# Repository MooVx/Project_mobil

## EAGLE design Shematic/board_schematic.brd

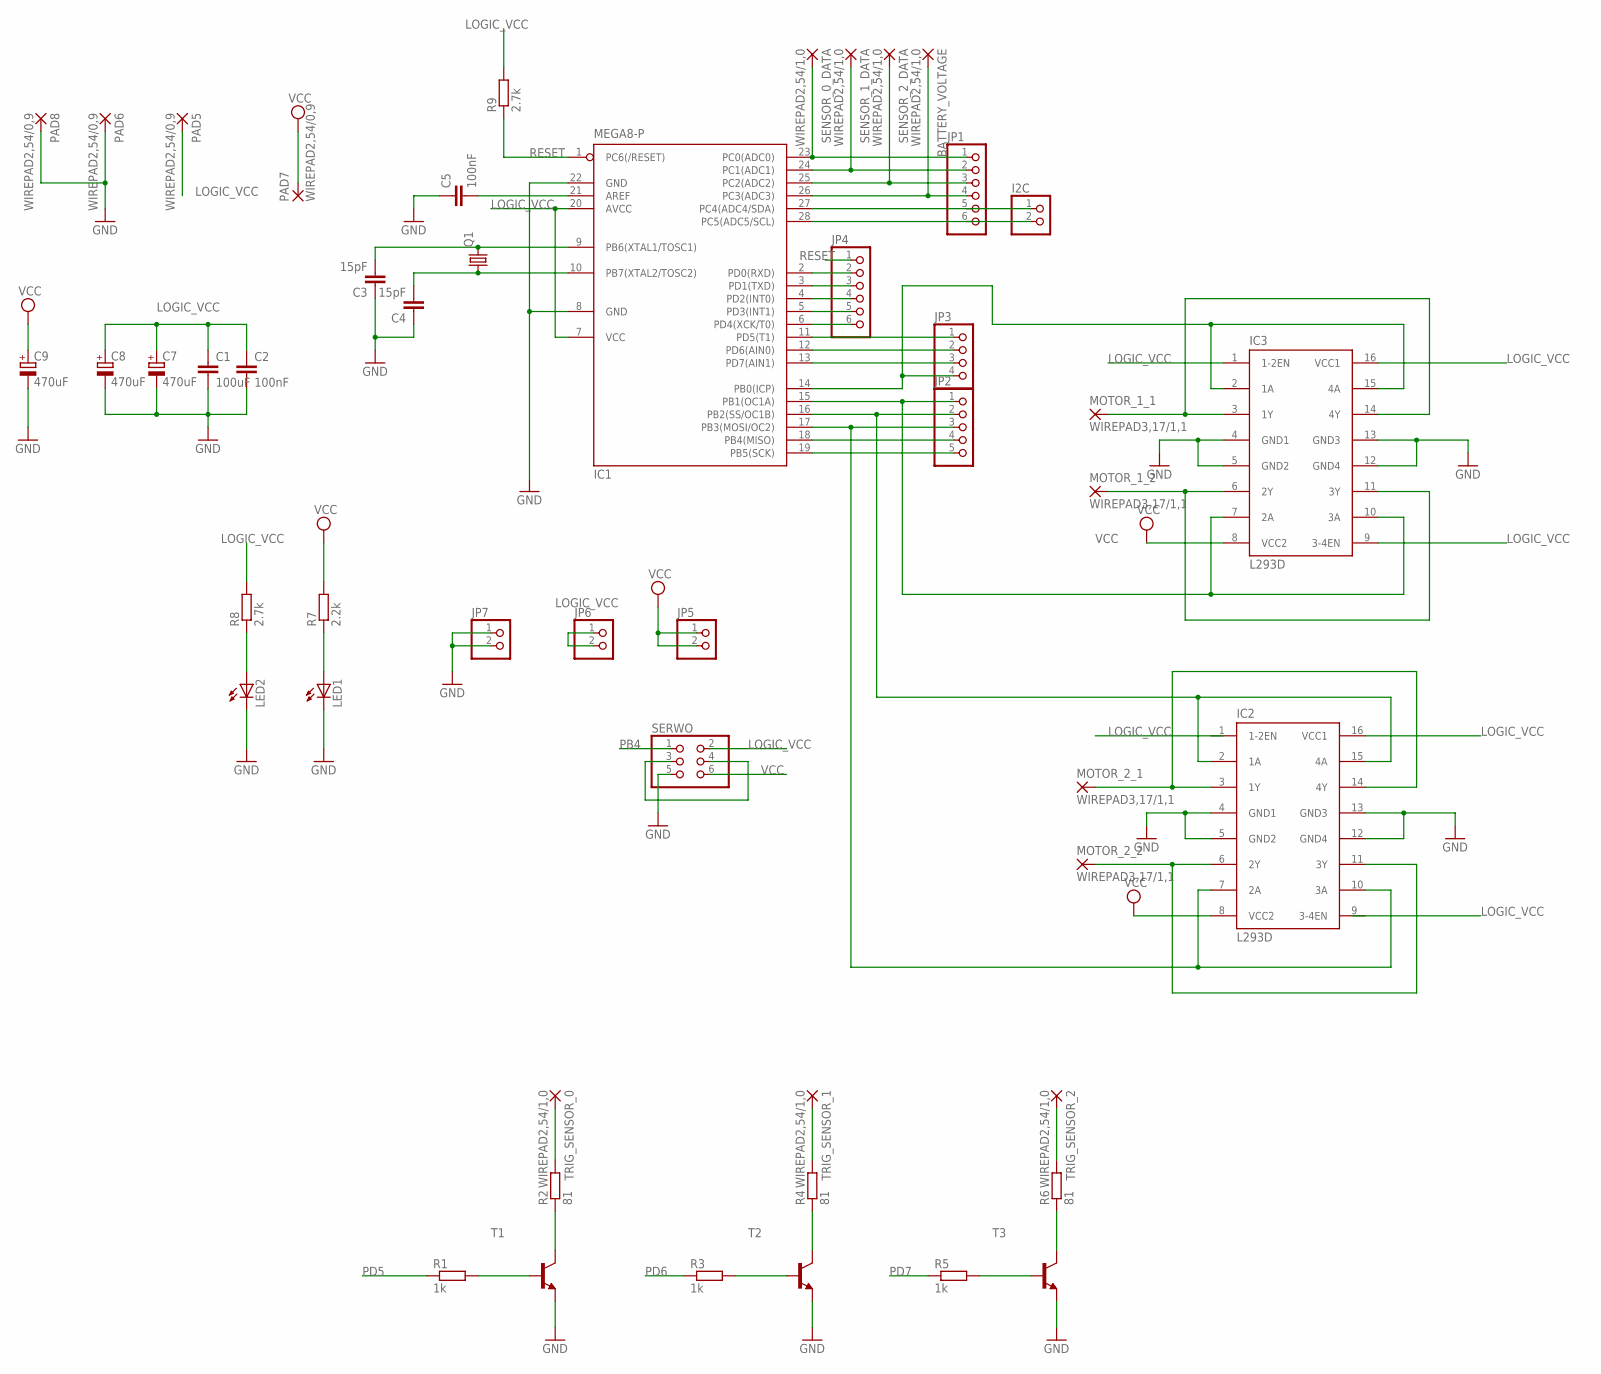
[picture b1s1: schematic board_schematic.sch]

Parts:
BATTERY_VOLTAGE: WIREPAD2,54/1,0; 2,54/1,0
C1: 100uF; C050-045X075
C2, C5: 100nF; C050-045X075
C3, C4: 15pF; C5B2.5
C7, C8, C9: 470uF; E3,5-8
I2C: PINHD-1X2; 1X02
IC1: MEGA8-P; DIL28-3
IC2, IC3: L293D; DIL16
JP1, JP4: PINHD-1X6; 1X06
JP2: PINHD-1X5; 1X05
JP3: PINHD-1X4; 1X04
JP5, JP6, JP7: PINHD-1X2; 1X02
LED1, LED2: LED5MM
MOTOR_1_1, MOTOR_1_2, MOTOR_2_1, MOTOR_2_2: WIREPAD3,17/1,1; 3,17/1,1
PAD5, PAD6, PAD7, PAD8: WIREPAD2,54/0,9; 2,54/0,9
Q1: CRYSTALHC49S; HC49/S
R1, R3, R5: 1k; 0204/7
R2, R4, R6: 81; 0204/7
R7: 2.2k; 0204/7
R8, R9: 2.7k; 0204/7
SENSOR_0_DATA, SENSOR_1_DATA, SENSOR_2_DATA: WIREPAD2,54/1,0; 2,54/1,0
SERWO: PINHD-2X3; 2X03
T1, T2, T3: 2N2222-NPN-TO92-EBC; TO92-EBC
TRIG_SENSOR_0, TRIG_SENSOR_1, TRIG_SENSOR_2: WIREPAD2,54/1,0; 2,54/1,0

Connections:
BLABLA: I2C.1, IC1.27 (PC4(ADC4/SDA)), JP1.5
GND: C1.2, C2.2, C3.1, C4.1, C5.1, C7.-, C8.-, C9.-, I2C.3, IC1.8 (GND), IC1.22 (GND), IC2.4 (GND1), IC2.5 (GND2), IC2.12 (GND4), IC2.13 (GND3), IC3.4 (GND1), IC3.5 (GND2), IC3.12 (GND4), IC3.13 (GND3), JP7.1, JP7.2, LED1.K (C), LED2.K (C), PAD6.1, PAD8.1, SERWO.5, T1.E, T2.E, T3.E
LOGIC_VCC: C1.1, C2.1, C7.+, C8.+, IC1.7 (VCC), IC1.20 (AVCC), IC2.1 (1-2EN), IC2.9 (3-4EN), IC2.16 (VCC1), IC3.1 (1-2EN), IC3.9 (3-4EN), IC3.16 (VCC1), JP6.1, JP6.2, PAD5.1, R8.2, R9.2, SERWO.2
unnamed: IC3.3 (1Y), IC3.14 (4Y), MOTOR_1_1.1
unnamed: IC1.15 (PB1(OC1A)), IC3.7 (2A), IC3.10 (3A), JP2.1
unnamed: IC2.3 (1Y), IC2.14 (4Y), MOTOR_2_1.1
unnamed: IC1.16 (PB2(SS/OC1B)), IC2.2 (1A), IC2.15 (4A), JP2.2
unnamed: R1.2, T1.B
unnamed: IC2.6 (2Y), IC2.11 (3Y), MOTOR_2_2.1
unnamed: IC3.6 (2Y), IC3.11 (3Y), MOTOR_1_2.1
unnamed: IC1.17 (PB3(MOSI/OC2)), IC2.7 (2A), IC2.10 (3A), JP2.3
unnamed: IC1.23 (PC0(ADC0)), JP1.1, SENSOR_0_DATA.1
unnamed: C3.2, IC1.9 (PB6(XTAL1/TOSC1)), Q1.2
unnamed: C4.2, IC1.10 (PB7(XTAL2/TOSC2)), Q1.1
unnamed: C5.2, IC1.21 (AREF)
unnamed: IC1.24 (PC1(ADC1)), JP1.2, SENSOR_1_DATA.1
unnamed: IC1.25 (PC2(ADC2)), JP1.3, SENSOR_2_DATA.1
unnamed: BATTERY_VOLTAGE.1, IC1.26 (PC3(ADC3)), JP1.4
unnamed: I2C.2, IC1.28 (PC5(ADC5/SCL)), JP1.6
unnamed: LED1.A, R7.1
unnamed: IC1.19 (PB5(SCK)), JP2.5
unnamed: IC1.6 (PD4(XCK/T0)), JP4.6
unnamed: IC1.5 (PD3(INT1)), JP4.5
unnamed: IC1.4 (PD2(INT0)), JP4.4
unnamed: IC1.3 (PD1(TXD)), JP4.3
unnamed: IC1.2 (PD0(RXD)), JP4.2
unnamed: SERWO.3, SERWO.4
unnamed: LED2.A, R8.1
unnamed: IC1.14 (PB0(ICP)), IC3.2 (1A), IC3.15 (4A), JP3.4
unnamed: R2.1, T1.C
unnamed: R2.2, TRIG_SENSOR_0.1
unnamed: R3.2, T2.B
unnamed: R4.1, T2.C
unnamed: R4.2, TRIG_SENSOR_1.1
unnamed: R5.2, T3.B
unnamed: R6.1, T3.C
unnamed: R6.2, TRIG_SENSOR_2.1
PB4: IC1.18 (PB4(MISO)), JP2.4, SERWO.1
PD5: IC1.11 (PD5(T1)), JP3.1, R1.1
PD6: IC1.12 (PD6(AIN0)), JP3.2, R3.1
PD7: IC1.13 (PD7(AIN1)), JP3.3, R5.1
RESET: IC1.1 (PC6(/RESET)), JP4.1, R9.1
VCC: C9.+, IC2.8 (VCC2), IC3.8 (VCC2), JP5.1, JP5.2, PAD7.1, R7.2, SERWO.6

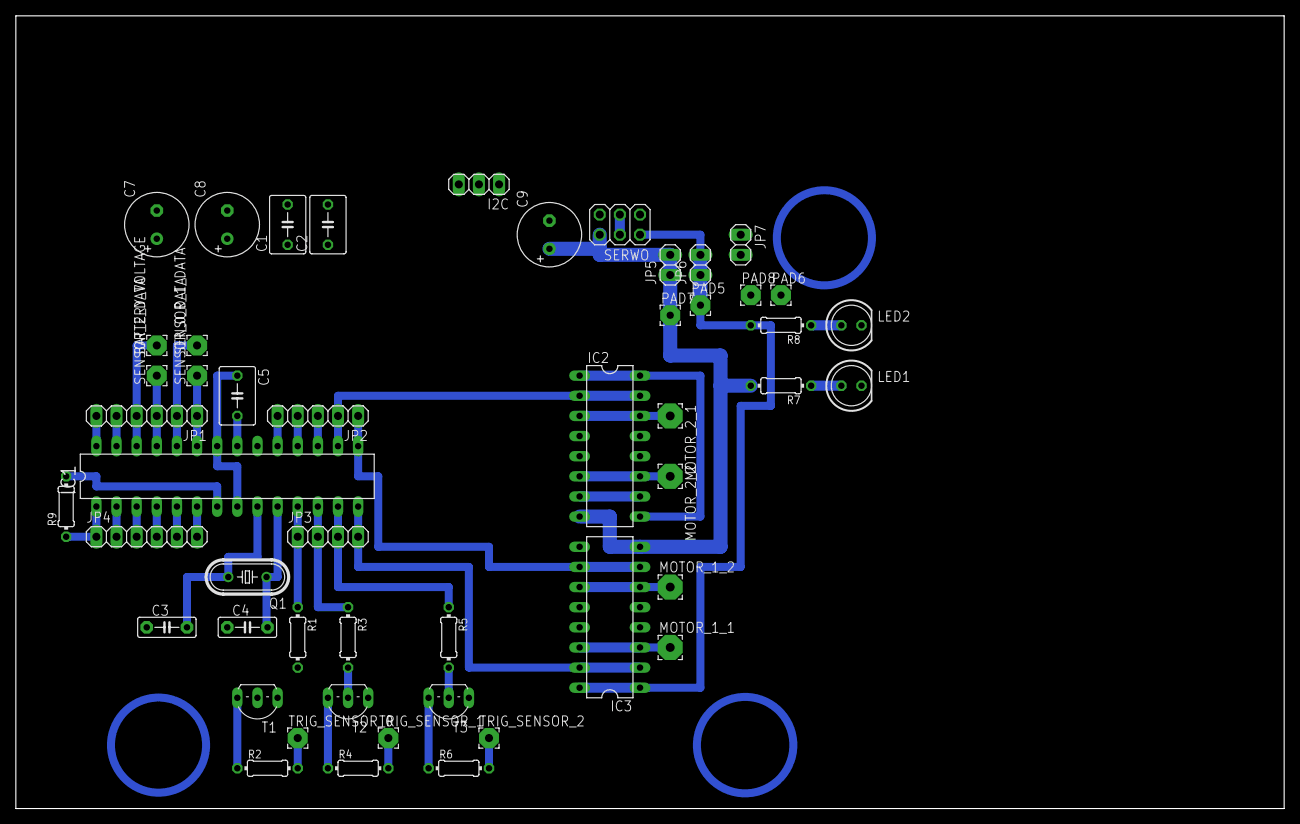
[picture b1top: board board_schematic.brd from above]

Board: 2 copper layers, 160.0 x 100.0 mm, 50 parts (0 on the bottom side), 43 nets.

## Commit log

2017-03-21 test
2017-03-21 shem
2017-03-23 added some outputs
2017-03-23 board start
2017-03-25 pcb shem finish
2017-03-25 Zdjecia do dokumentacji
    Schematy poszczegolnych sekcji + PDF zawierajacy caly schemat.
2017-03-25 Updata
    Wykonana plytka
2017-03-25 Sprawko + dokumentacja
    Gotowe do wyslania ;-)
2017-04-05 Sprawko - Etap2
2017-04-27 spr3
